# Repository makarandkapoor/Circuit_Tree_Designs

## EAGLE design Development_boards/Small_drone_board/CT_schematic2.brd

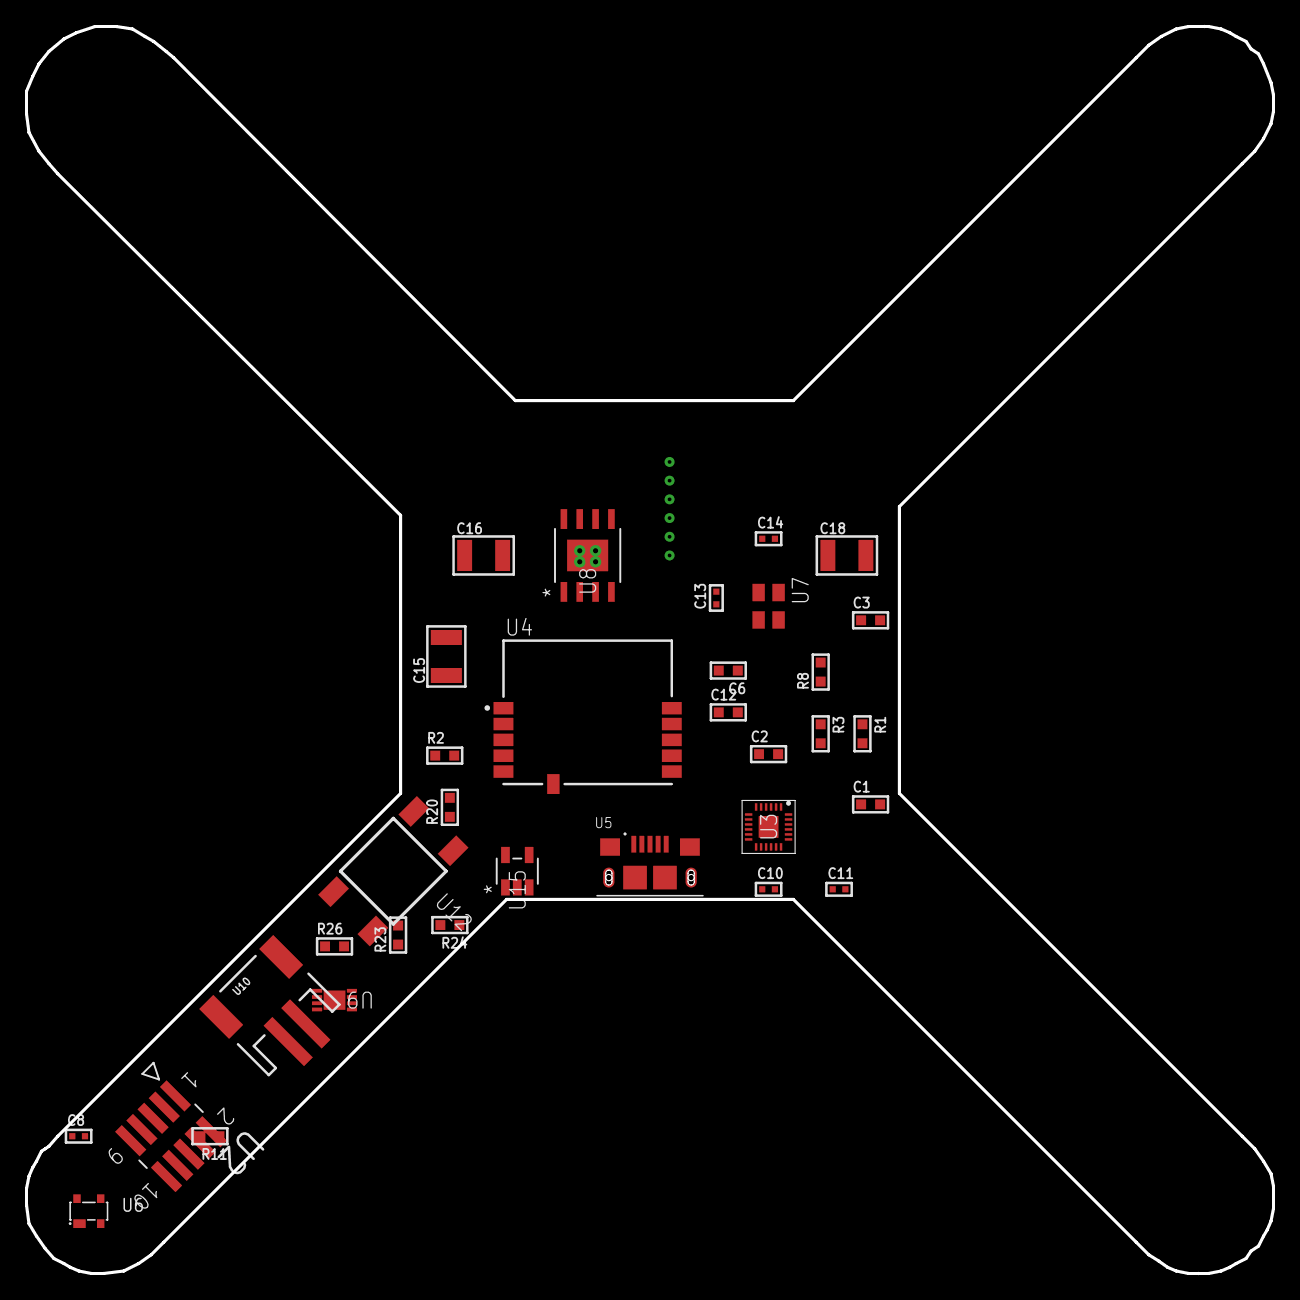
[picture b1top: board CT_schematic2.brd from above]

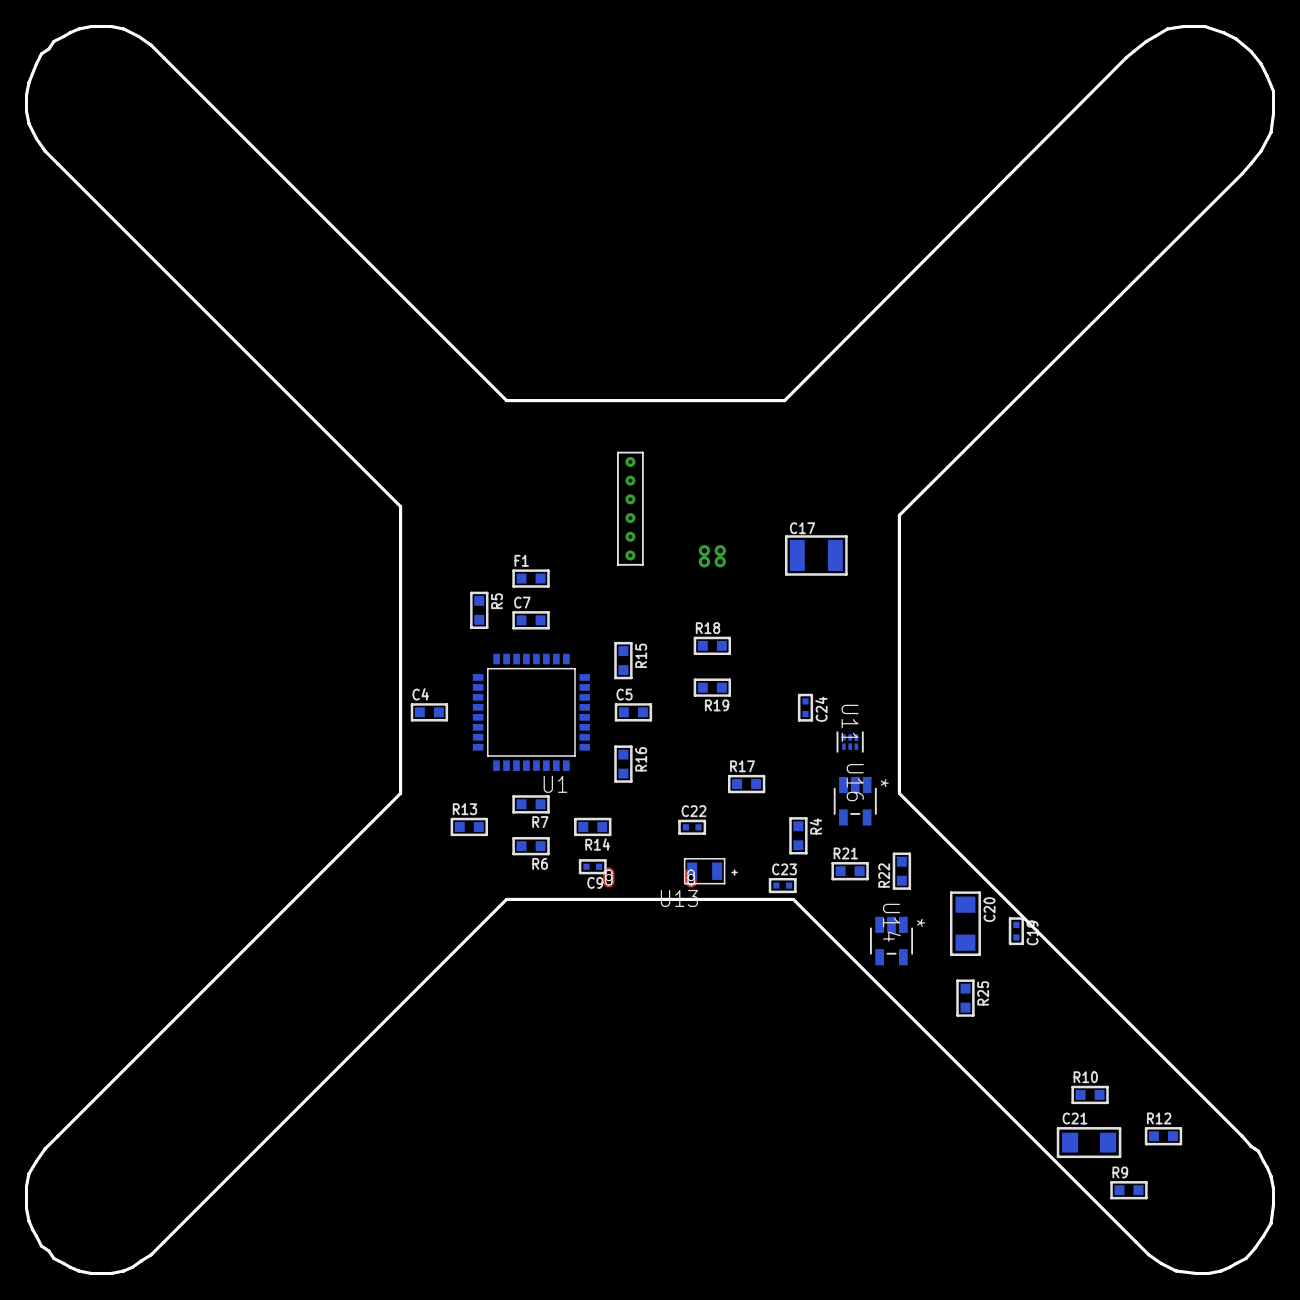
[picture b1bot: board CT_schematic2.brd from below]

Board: 2 copper layers, 100.0 x 100.0 mm, 68 parts (35 on the bottom side), 40 nets, no tracks yet.

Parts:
C1: c1; C0603
C2: c2; C0603
C3: c3; C0603
C4: c4; C0603
C5: c5; C0603
C6: c6; C0603
C7: c7; C0603
C8: c8; C0402
C9: c9; C0402
C10: c10; C0402
C11: c11; C0402
C12: c12; C0603
C13: c13; C0402
C14: c14; C0402
C15: c15; C1210
C16: c16; C1210
C17: c17; C1210
C18: c18; C1210
C19: c19; C0402
C20: c20; C1206
C21: c21; C1206
C22: c22; C0402
C23: c23; C0402
C24: c24; C0402
F1: f1; L0603
R1: r1; R0603
R2: r2; R0603
R3: r3; R0603
R4: r4; R0603
R5: r5; R0603
R6: r6; R0603
R7: r7; R0603
R8: r8; R0603
R9: r9; R0603
R10: r10; R0603
R11: r11; R0603
R12: r12; R0603
R13: r13; R0603
R14: r14; R0603
R15: r15; R0603
R16: r16; R0603
R17: r17; R0603
R18: r18; R0603
R19: r19; R0603
R20: r20; R0603
R21: r21; R0603
R22: r22; R0603
R23: r23; R0603
R24: r24; R0603
R25: r25; R0603
R26: r26; R0603
U1: u1; LQFP32
U2: u2; SAMTEC_FTSH-105-01-L-DV-K
U3: u3; QFN24_2
U4: u4; XCVR_SPBTLE-RF
U5: u5; FCI_10118193-0001LF
U6: u6; SOT143B
U7: u7; ASEK
U8: u8; SOIC-8_EP
U9: u9; DFN8_2X3MC
U10: u10; JST-2-SMD
U11: u11; SON-6
U12: u12; SW_4-1437565-2
U13: u13; LGM67K-G1J2-24-Z
U14: u14; NC7SZ125M5X
U15: u15; NC7SZ125M5X
U16: u16; NC7SZ125M5X
U17: u17; DUMMY_PACKAGE_150

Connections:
CLK_U1_2: U1.2, U7.3
GND: C1.2, C2.2, C3.2, C4.2, C5.2, C6.2, C7.2, C8.2, C9.2, C10.2, C11.2, C12.2, C13.2, C14.2, C15.2, C16.2, C17.2, C18.2, C19.2, C20.2, C21.2, C22.2, C23.2, C24.2, R2.2, R8.2, R12.2, R16.2, R17.2, R19.2, R22.2, R24.2, R25.2, U1.16, U1.32, U2.3, U2.5, U3.18, U3.20, U3.25, U4.6, U5.5, U5.6, U5.7, U5.8, U5.9, U6.1, U7.2, U8.7, U8.EPAD, U9.6, U9.9, U10.2, U11.2, U13.C, U14.2, U14.3, U15.1, U15.3, U16.1, U16.3, U17.1
INPUT_USBPOWER_5V: C20.1, R26.2, U5.1, U6.4, U9.1, U9.2
NET_U1_4: R5.1, U1.4, U16.4
NET_U1_5: C6.1, C7.1, F1.1, U1.5
NET_U1_27: R3.1, U1.27, U13.A
NET_U1_28: R1.1, U1.28, U12.3, U12.4
NET_U1_29: R6.1, U1.29, U3.23
NET_U1_30: R7.1, U1.30, U3.24
NET_U1_31: R8.1, U1.31
NET_U2_9: R12.1, U2.9
NET_U3_9: R14.1, U3.9
NET_U3_10: C9.1, U3.10
NET_U3_22: R13.1, U3.22
NET_U4_11: R4.1, U4.11, U15.4
NET_U8_4: R18.2, R19.1, U8.4
NET_U9_5: R26.1, U9.5
NET_U9_8: R25.1, U9.8
NET_U11_1: R21.1, R22.1, U11.1
NET_U11_3: R23.2, R24.1, U11.3
NET_U11_4: R20.1, U11.4, U14.4, U15.2, U16.2
NET_U12_1: R2.1, U12.1, U12.2
PROC_GPIO_TO_U3_FSYNC: U1.6, U3.11
PROC_GPIO_TO_U3_INT_B: U1.3, U3.12
PROC_GPIO_TO_U4_SPI_IRQ: R17.1, U1.7, U4.4
PROC_PA2: U1.8, U17.2
PROC_PA3: U1.9, U17.3
PROC_PB0: U1.14, U17.4
PROC_PB1: U1.15, U17.5
PROC_SPI1_MISO: U1.12, U4.8
PROC_SPI1_MOSI: U1.13, U4.9
PROC_SPI1_NSS: R15.1, U1.10, U4.10
PROC_SPI1_SCK: R16.1, U1.11, U4.7
PROC_SYS_SWCLK: R10.1, U1.24, U2.4
PROC_SYS_SWDIO: R11.1, U1.23, U2.2
PROC_USB_DM: U1.21, U5.2, U6.3
PROC_USB_DP: U1.22, U5.3, U6.2
RST_OUT_U2_JTAG_RST_B: R9.1, U2.10, U14.1
VCC_S1_3V7: C15.1, C16.1, C21.1, U8.5, U8.8, U9.3, U9.4, U10.1
VCC_TIER1_3V3: C1.1, C2.1, C3.1, C4.1, C5.1, C8.1, C10.1, C11.1, C12.1, C13.1, C14.1, C17.1, C18.1, C19.1, C22.1, C23.1, C24.1, F1.2, R1.2, R3.2, R4.2, R5.2, R6.2, R7.2, R9.2, R10.2, R11.2, R13.2, R14.2, R15.2, R18.1, R20.2, R21.2, R23.1, U1.1, U1.17, U2.1, U3.1, U3.8, U3.13, U4.5, U7.4, U8.1, U11.6, U14.5, U15.5, U16.5

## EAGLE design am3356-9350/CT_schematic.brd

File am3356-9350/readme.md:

## Introduction
This design is a demo design example auto generated through scripts at circuit-tree.com server. 
Circuit Tree designs are dynamic which means designs, symbols and placement is generated dynamically
The scripts randonly selects parts, peripheral interfaces, type and value of power input to the board to be created.

## Folder contents
In this folder eagle, altium and orcad schematic files , bill of material, board component placement file 
pictures from various dxf file which are auto generated through circuit tree server are present.

## Additional references
Generate embedded hardware designs through [Circuit Tree](http://circuit-tree.com/) schematics and board placement file instantly. 
Use autorouter to complete your the final board file.

## Circuit Description
Circuit Description: Design uses a controller from Texas Instruments with part number AM3356BZCZA80 and following parts in the 
design:
- 10100565 from Amphenol
- FTSH-105-01-L-DV-K from Samtec
- LAN8710AI-EZK from Microchip
- 7498011122R from WURTH ELEKTRONIK
- AT24C02D-SSHM-T from Atmel
- S29VS256RABBHW000 from Spansion
- ABS07-32.768KHZ-7-T from ABRACON
- ABLS-25.000MHZ-B2F-T from ABRACON
- ASDMB-24.000MHZ-EC-T from abracon
- LP2954AIMX/NOPB from TI
- LP3878SDX-ADJ/NOPB  from TI
- LP2951ACSDX/NOPB from TI
- LP3878SDX-ADJ/NOPB  from TI
- LTC3601EUD#PBF from Linear Tech
- LTC3601EUD#PBF from Linear Tech
- LTC3601EUD#PBF from Linear Tech
- LTC2928CUHF#PBF from Linear Tech
- IRF8306MTRPbF from Infineon
- IRF8306MTRPbF from Infineon
- IRF8306MTRPbF from Infineon
- IRF8306MTRPbF from Infineon
- PJ-037B from CUI Inc.
- 4-1437565-2 from TE connectivity
- Q65110A2395 from osram
- nc7sz125m5x from On Semi
- nc7sz125m5x from On Semi
- nc7sz125m5x from On Semi
- nc7sz125m5x from On Semi

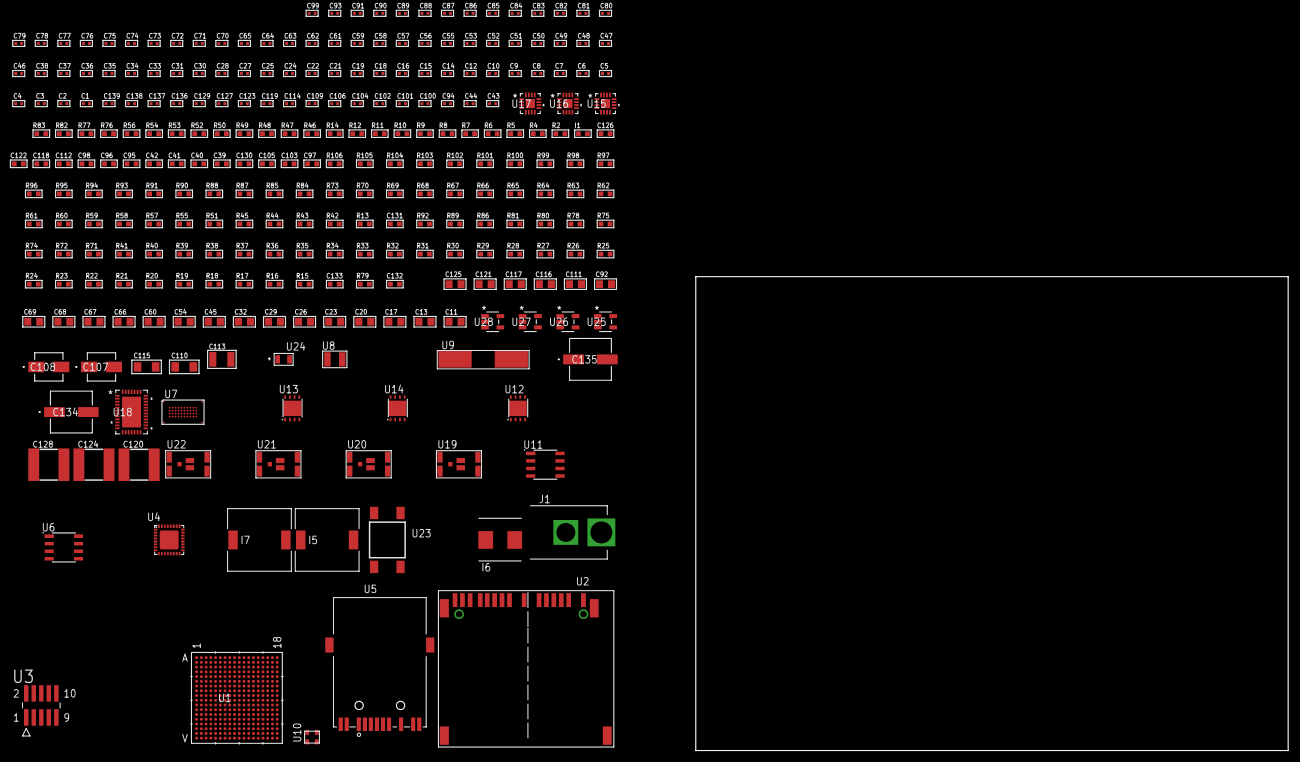
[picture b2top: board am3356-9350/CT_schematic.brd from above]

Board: 2 copper layers, 100.0 x 80.0 mm, 276 parts (0 on the bottom side), 180 nets, no tracks yet.

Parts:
C1, C6, C7, C65, C70, C71, C72, C73, C74, C75, C76, C77, C78, C79, C80, C81, C82, C83, C84, C85, C86, C87, C88, C89, C90, C91, C93, C102, C104, C119, C123, C127, C129: 1e-07; C0402
C2, C3, C4, C5, C8, C9, C10, C12, C14, C15, C16, C18, C19, C21, C22, C24, C25, C27, C28, C30, C31, C33, C34, C35, C36, C37, C38, C46, C47, C48, C49, C50, C51, C52, C53, C55, C56, C57, C58, C59, C61, C62, C63, C64, C101, C106, C109, C114, C136, C137, C138, C139: 1e-08; C0402
C11, C13, C17, C20, C23, C26, C29, C32, C45, C54, C60, C66, C67, C68, C69, C92, C111, C116, C117, C121, C125: 1e-05; C0805
C39, C40, C41, C42, C95, C96, C98, C112, C118, C122, C126: 1e-06; C0603
C43, C44: 1.2e-11; C0402
C94: 2.2e-08; C0402
C97: 4.7e-10; C0603
C99, C100: 1e-11; C0402
C103, C105, C130: 2.2e-06; C0603
C107: 1e-06; EXV-9B
C108: 2.2e-06; EXV-9B
C110, C115: 1e-05; C1206
C113: 1e-05; C1210
C120, C124, C128: 6.8e-05; 2220
C131: 2.45e-08; R0603
C132: 2.8258362168397e-09; R0603
C133: 7.105e-09; R0603
C134, C135: 0.0001; EXV-9H
I1: 97.0; R0603
I5: 2.5e-06; DR1040
I6: 3.3e-06; WE-HCI_7030/7040/7050
I7: 3.8e-06; DR1040
J1: PJ-037B; PJ-037B_PACKAGE
R2, R77, R83: 1000.0; R0603
R4, R5, R6, R7: 4700.0; R0603
R8, R9, R10, R11: 2200.0; R0603
R12: 22.0; R0603
R13, R42, R43, R44, R45, R55, R57, R58, R59, R60, R61, R62, R63, R64, R65, R66, R67, R68, R69, R70, R93, R95, R96, R101, R102, R103, R104, R105: 10000.0; R0603
R14, R52, R53, R54, R56: 49.9; R0603
R15, R16, R17, R18, R19, R20, R21, R22, R23, R24, R25, R26, R27, R28, R29, R30, R31, R32, R33, R34, R35, R36, R37, R38, R39, R40, R41, R71, R72, R74, R75, R78, R80, R81: 100000.0; R0603
R46: 5.0; R0603
R47, R48: 0.1; R0603
R49, R50: 200.0; R0603
R51: 12100.0; R0603
R73: 47000.0; R0603
R76: 360.0; R0603
R79: 153694.38; R0603
R82: 100.0; R0603
R84, R87, R90: 20000.0; R0603
R85: 22600.0; R0603
R86, R89, R92: 300000.0; R0603
R88: 39000.0; R0603
R91: 91000.0; R0603
R94, R106: 75000.0; R0603
R97, R98, R99, R100: 95300.0; R0603
U1: AM3356BZCZA80; LFBGA324
U2: 10100565
U3: FTSH-105-01-L-DV-K; SAMTEC_FTSH-105-01-L-DV-K
U4: LAN8710AI-EZK; QFN-32
U5: 7498011122R
U6: AT24C02D-SSHM-T; AT24C02D
U7: S29VS256RABBHW000
U8: ABS07-32.768KHZ-7-T
U9: ABLS-25.000MHZ-B2F-T
U10: ASDMB-24.000MHZ-EC-T; ASDMB-XX.XXXXMHZ-XX-XX-XXX
U11: LP2954AIMX/NOPB; LP2954
U12, U14: LP3878SDX-ADJ/NOPB; WSON-8
U13: LP2951ACSDX/NOPB; WSON-8
U15, U16, U17: LTC3601EUD#PBF; QFN-16_EP
U18: LTC2928CUHF#PBF; QFN-38_UHF
U19, U20, U21, U22: IRF8306MTRPbF; IRF8306MTRPBF
U23: 4-1437565-2; SW_4-1437565-2
U24: Q65110A2395; LGM67K-G1J2-24-Z
U25, U26, U27, U28: nc7sz125m5x; NC7SZ125M5X

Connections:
CLK_CRYSTAL_U1_A4: C44.1, U1.A4, U8.2
CLK_CRYSTAL_U1_A6: C43.1, U1.A6, U8.1
CLK_CRYSTAL_U4_4: C100.1, U4.4, U9.2
CLK_CRYSTAL_U4_5: C99.1, U4.5, U9.1
CLK_U1_V10: U1.V10, U10.3
GND: C1.2, C2.2, C3.2, C4.2, C5.2, C6.2, C7.2, C8.2, C9.2, C10.2, C11.2, C12.2, C13.2, C14.2, C15.2, C16.2, C17.2, C18.2, C19.2, C20.2, C21.2, C22.2, C23.2, C24.2, C25.2, C26.2, C27.2, C28.2, C29.2, C30.2, C31.2, C32.2, C33.2, C34.2, C35.2, C36.2, C37.2, C38.2, C39.2, C40.2, C41.2, C42.2, C43.2, C44.2, C45.2, C46.2, C47.2, C48.2, C49.2, C50.2, C51.2, C52.2, C53.2, C54.2, C55.2, C56.2, C57.2, C58.2, C59.2, C60.2, C61.2, C62.2, C63.2, C64.2, C65.2, C66.2, C67.2, C68.2, C69.2, C70.2, C71.2, C72.2, C73.2, C74.2, C75.2, C76.2, C77.2, C78.2, C79.2, C80.2, C81.2, C82.2, C83.2, C84.2, C85.2, C86.2, C87.2, C88.2, C89.2, C90.2, C91.2, C92.2, C93.2, C94.2, C95.2, C96.2, C97.2, C98.2, C99.2, C100.2, C101.2, C102.2, C103.2, C104.2, C105.2, C106.2, C107.2, C108.2, C109.2, C110.2, C111.2, C112.2, C113.2, C114.2, C115.2, C116.2, C117.2, C118.2, C120.1, C120.2, C121.2, C122.2, C124.1, C124.2, C125.2, C126.2, C128.1, C128.2, C129.2, C130.2, C131.2, C132.2, C133.2, C134.2, C135.2, C136.2, C137.2, C138.2, C139.2, J1.2, R2.2, R13.2, R14.2, R21.2, R22.2, R24.2, R25.2, R26.2, R27.2, R28.2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
NET_U1_A10: R6.1, U1.A10, U28.4
NET_U1_B4: R13.1, U1.B4
NET_U1_C10: C42.1, U1.C10
NET_U1_C16: R8.1, U1.C16, U6.6
NET_U1_C17: R9.1, U1.C17, U6.5
NET_U1_D6: C40.1, U1.D6
NET_U1_D9: C39.1, U1.D9
NET_U1_D11: C41.1, U1.D11
NET_U1_F15: U23.3, U23.4
NET_U1_J3: R14.1, U1.J3
NET_U1_J4: C1.1, C6.1, C7.1, U1.J4
NET_U1_M17: R11.1, U1.M17, U4.16
NET_U1_M18: R10.1, U1.M18, U4.17
NET_U1_R1: R15.1, U1.R1
NET_U1_R2: R16.1, U1.R2
NET_U1_R3: R17.1, U1.R3
NET_U1_R4: R18.1, U1.R4
NET_U1_R15: C5.1, U1.R15
NET_U1_R16: C4.1, U1.R16
NET_U1_T1: R19.1, U1.T1
NET_U1_T2: R20.1, U1.T2
NET_U1_T3: R21.1, U1.T3
NET_U1_T4: R22.1, U1.T4
NET_U1_U1: R23.1, U1.U1
NET_U1_U2: R24.1, U1.U2
NET_U1_U3: R25.1, U1.U3
NET_U1_U4: R26.1, U1.U4
NET_U1_V2: R27.1, U1.V2
NET_U2_18: U2.18, U2.19
NET_U3_9: R46.1, U3.9
NET_U4_1: C95.1, I1.1, R52.2, R53.2, R54.2, R56.2, U4.1, U4.27
NET_U4_6: C96.1, C97.1, U4.6
NET_U4_18: R55.1, U4.18
NET_U4_19: R4.1, U4.19, U26.4
NET_U4_32: R51.1, U4.32
NET_U5_1: R52.1, U4.29, U5.1
NET_U5_3: R50.2, R53.1, U4.28, U5.3
NET_U5_4: R54.1, U4.31, U5.4
NET_U5_5: C94.1, U5.2, U5.5
NET_U5_6: R56.1, U4.30, U5.6
NET_U5_8: R48.1, U5.8
NET_U5_9: R50.1, U5.9
NET_U5_11: U4.2, U5.11
NET_U5_12: R49.1, U5.12
NET_U5_13: R47.1, U5.13, U5.14
NET_U6_1: R64.1, U6.1
NET_U6_2: R65.1, U6.2
NET_U6_3: R66.1, U6.3
NET_U6_7: R63.1, U6.7
NET_U7_D8: R5.1, U7.D8, U27.4
NET_U11_3: R72.1, U11.3
NET_U11_5: R71.1, U11.5
NET_U11_7: R73.2, R74.1, U11.7
NET_U12_1: C109.1, U12.1
NET_U12_6: R76.2, R77.1, U12.6
NET_U12_8: R75.1, U12.8
NET_U13_5: R78.1, U13.5
NET_U13_7: R79.2, R80.1, U13.7
NET_U14_1: C114.1, U14.1
NET_U14_6: R82.2, R83.1, U14.6
NET_U14_8: R81.1, U14.8
NET_U15_3: C119.2, I5.1, U15.3, U15.4
NET_U15_6: C119.1, U15.6
NET_U15_7: C118.1, U15.7, U15.12
NET_U15_10: R86.1, U15.10
NET_U15_11: R84.1, R85.1, U15.11
NET_U15_ATNET_3: I5.2, R85.2
NET_U16_3: C123.2, I6.1, U16.3, U16.4
NET_U16_6: C123.1, U16.6
NET_U16_7: C122.1, U16.7, U16.12
NET_U16_10: R89.1, U16.10
NET_U16_11: R87.1, R88.1, U16.11
NET_U16_ATNET_3: I6.2, R88.2
NET_U17_3: C127.2, I7.1, U17.3, U17.4
NET_U17_6: C127.1, U17.6
NET_U17_7: C126.1, U17.7, U17.12
NET_U17_10: R92.1, U17.10
NET_U17_11: R90.1, R91.1, U17.11
NET_U17_ATNET_3: I7.2, R91.2
NET_U18_3: R102.1, U18.3
NET_U18_6: R97.1, U18.6
NET_U18_7: R98.1, U18.7
NET_U18_8: R99.1, U18.8
NET_U18_9: R100.1, U18.9
NET_U18_16: R101.1, R106.1, U18.16
NET_U18_18: R96.1, U18.18
NET_U18_19: R95.1, U18.19, U18.20
NET_U18_21: R93.1, R94.1, U18.21, U25.4, U26.2, U27.2, U28.2
NET_U18_22: C129.1, R93.2, R95.2, R96.2, U18.11, U18.22
NET_U18_26: C132.1, U18.26
NET_U18_27: C131.1, U18.27
NET_U18_28: C133.1, U18.28
NET_U18_30: R105.1, U18.30
NET_U18_32: R104.1, U18.32
NET_U18_38: R103.1, U18.38
NET_U19_3: U18.2, U19.3
NET_U20_3: U18.37, U20.3
NET_U21_3: U18.31, U21.3
NET_U22_3: U18.29, U22.3
NET_U23_1: R2.1, U23.1, U23.2
PROC_GPMC_A17: R28.1, U1.V3, U7.D4
PROC_GPMC_A18: R29.1, U1.V4, U7.C11
PROC_GPMC_A19: R30.1, U1.T5, U7.D10
PROC_GPMC_A20: U1.R14, U7.C10
PROC_GPMC_A21: U1.V15, U7.D5
PROC_GPMC_A22: U1.G15, U7.C4
PROC_GPMC_A23: U1.G16, U7.C12
PROC_GPMC_A24: U1.G17, U7.D7
PROC_GPMC_AD0: U1.U7, U7.F3
PROC_GPMC_AD1: U1.V7, U7.F4
PROC_GPMC_AD2: U1.R8, U7.E6
PROC_GPMC_AD3: U1.T8, U7.E7
PROC_GPMC_AD4: U1.U8, U7.F8
PROC_GPMC_AD5: U1.V8, U7.F9
PROC_GPMC_AD6: U1.R9, U7.E10
PROC_GPMC_AD7: U1.T9, U7.E11
PROC_GPMC_AD8: U1.U10, U7.E4
PROC_GPMC_AD9: U1.T10, U7.E5
PROC_GPMC_AD10: U1.T11, U7.F6
PROC_GPMC_AD11: U1.U12, U7.F7
PROC_GPMC_AD12: U1.T12, U7.E8
PROC_GPMC_AD13: U1.R12, U7.E9
PROC_GPMC_AD14: U1.V13, U7.F11
PROC_GPMC_AD15: U1.U13, U7.F12
PROC_GPMC_ADVN_ALE: U1.R7, U7.D6
PROC_GPMC_CLK: U1.U9, U7.C6
PROC_GPMC_CSN0: R68.1, U1.V6, U7.D11
PROC_GPMC_OEN_REN: R70.1, U1.T7, U7.E12
PROC_GPMC_WAIT0: R67.1, U1.T17, U7.C3
PROC_GPMC_WEN: R69.1, U1.U6, U7.C8
PROC_MII1_COL: R59.1, U1.H16, U4.15
PROC_MII1_CRS: U1.H17, U4.14
PROC_MII1_RXD0: R57.1, U1.M16, U4.11
PROC_MII1_RXD1: R58.1, U1.L15, U4.10
PROC_MII1_RXD2: U1.L16, U4.9
PROC_MII1_RXD3: R62.1, U1.L17, U4.8
PROC_MII1_RX_CLK: R61.1, U1.L18, U4.7
PROC_MII1_RX_DV: U1.J17, U4.26
PROC_MII1_RX_ER: R60.1, U1.J15, U4.13
PROC_MII1_TXD0: U1.K17, U4.22
PROC_MII1_TXD1: U1.K16, U4.23
PROC_MII1_TXD2: U1.K15, U4.24
PROC_MII1_TXD3: U1.J18, U4.25
PROC_MII1_TX_CLK: U1.K18, U4.20
PROC_MII1_TX_EN: U1.J16, U4.21
PROC_MMC2_CLK: R12.2, R31.1, U1.V12, U2.8
PROC_MMC2_CLK_R: R12.1, U1.V12
PROC_MMC2_DAT0: R34.1, U1.V14, U2.4
PROC_MMC2_DAT1: R35.1, U1.U14, U2.3
PROC_MMC2_DAT2: R36.1, U1.T14, U2.15
PROC_MMC2_DAT3: R37.1, U1.U18, U2.14
PROC_MMC2_DAT4: R38.1, U1.U15, U2.13
PROC_MMC2_DAT5: R39.1, U1.T15, U2.11
PROC_MMC2_DAT6: R40.1, U1.V16, U2.7
PROC_MMC2_DAT7: R41.1, U1.U16, U2.5
PROC_MMC2_SDCD: R32.1, U1.U17, U2.2
PROC_MMC2_SDWP: R33.1, U1.A16, U2.1
PROC_TCK: R45.1, U1.A12, U3.4
PROC_TDI: R43.1, U1.B11, U3.8
PROC_TDO: U1.A11, U3.6
PROC_TMS: R44.1, U1.C11, U3.2
RST_OUT_U3_JTAG_RST_B: R42.1, U3.10, U25.1
VCC_9V3: C130.1, C134.1, C135.1, J1.1, R106.2, U18.23, U19.1, U19.2, U19.6, U19.7, U20.1, U20.2, U20.6, U20.7, U21.1, U21.2, U21.6, U21.7, U22.1, U22.2, U22.6, U22.7
VCC_S1_9V3: C107.1, R72.2, U11.8, U19.4, U19.5
VCC_S2_9V3: C110.1, R75.2, U12.4, U20.4, U20.5
VCC_S3_9V3: C112.1, U13.8, U21.4, U21.5
VCC_S4_9V3: C115.1, C117.1, C121.1, C125.1, R81.2, U14.4, U15.15, U15.16, U16.15, U16.16, U17.15, U17.16, U22.4, U22.5
VCC_TIER1_1V8: C2.1, C8.1, C9.1, C10.1, C11.1, C12.1, C13.1, C14.1, C15.1, C16.1, C60.1, C61.1, C62.1, C63.1, C64.1, C91.1, C92.1, C106.1, C108.1, C136.1, C137.1, C138.1, C139.1, R31.2, R32.2, R33.2, R34.2, R35.2, R36.2, R37.2, R38.2, R39.2, R40.2, R41.2, R71.2, R73.1, U1.D7, U1.D10, U1.E6, U1.E7, U1.E9, U1.E14, U1.F9, U1.H15, U1.K13, U1.N6, U1.N16, U1.P9, U1.P14, U1.R10, U1.R11, U2.9, U10.4, U11.1, U25.5, U26.5, U27.5, U28.5
VCC_TIER2_1V35: C65.1, C66.1, C67.1, C68.1, C69.1, C70.1, C71.1, C72.1, C73.1, C74.1, C75.1, C76.1, C77.1, C78.1, C79.1, C80.1, C81.1, C82.1, C83.1, C84.1, C85.1, C86.1, C87.1, C88.1, C89.1, C90.1, C111.1, R76.1, U1.E5, U1.F5, U1.G5, U1.H5, U1.J5, U1.K5, U1.L5, U12.5
VCC_TIER3_3V3: C3.1, C113.1, R78.2, R79.1, U1.N15, U13.1
VCC_TIER4_1V1: C45.1, C46.1, C47.1, C48.1, C49.1, C50.1, C51.1, C52.1, C53.1, C116.1, R82.1, U1.F6, U1.F7, U1.G6, U1.G7, U1.G10, U1.H11, U1.J12, U1.K6, U1.K8, U1.K12, U1.L6, U1.L7, U1.L8, U1.L9, U1.M11, U1.M13, U1.N8, U1.N9, U1.N12, U1.N13, U14.5
VCC_TIER4_1V8: C17.1, C18.1, C19.1, C20.1, C21.1, C22.1, C23.1, C24.1, C25.1, C26.1, C27.1, C28.1, C29.1, C30.1, C31.1, C32.1, C33.1, C34.1, C35.1, C36.1, C37.1, C38.1, C93.1, C98.1, C101.1, C102.1, C103.1, C104.1, C105.1, C124.2, I6.2, R4.2, R5.2, R6.2, R7.2, R8.2, R9.2, R10.2, R11.2, R15.2, R16.2, R17.2, R18.2, R19.2, R20.2, R23.2, R42.2, R43.2, R44.2, R55.2, R57.2, R58.2, R59.2, R60.2, R61.2, R64.2, R67.2, R68.2, R69.2, R70.2, R88.2, U1.E10, U1.E11, U1.E12, U1.E13, U1.F14, U1.G14, U1.H14, U1.J14, U1.K14, U1.L14, U1.N5, U1.P5, U1.P6, U1.P7, U1.P8, U1.P10, U1.P11, U1.P12, U1.P13, U3.1, U4.12, U6.8, U7.C7, U7.D3, U7.F10, U16.8
VCC_TIER4_1V26: C54.1, C55.1, C56.1, C57.1, C58.1, C59.1, C120.2, I5.2, R85.2, U1.A2, U1.F10, U1.F11, U1.F12, U1.F13, U1.G13, U1.H13, U1.J13, U15.8
VCC_TIER4_3V3: C128.2, I1.2, I7.2, R91.2, U17.8

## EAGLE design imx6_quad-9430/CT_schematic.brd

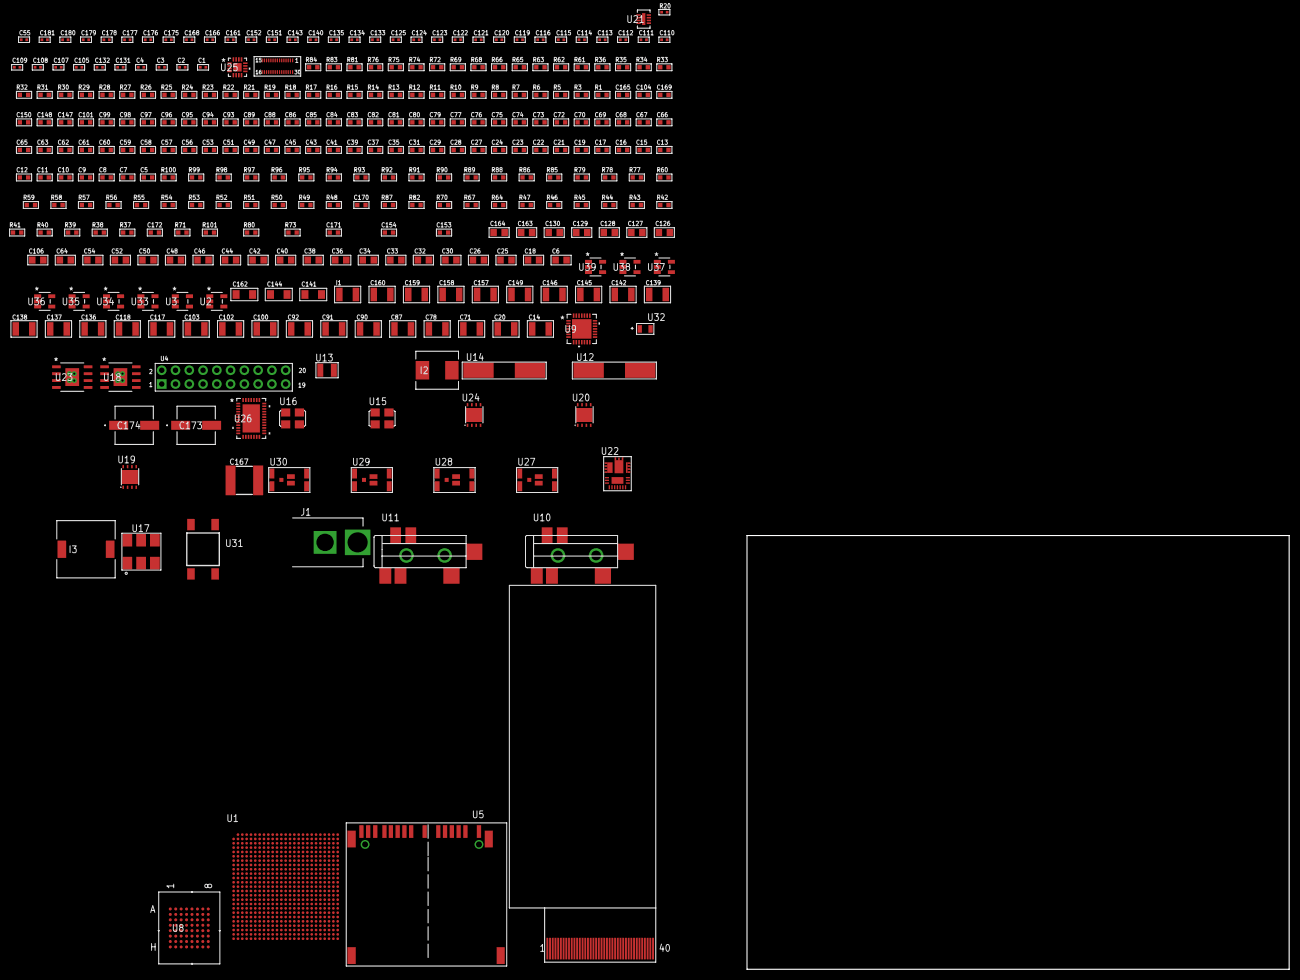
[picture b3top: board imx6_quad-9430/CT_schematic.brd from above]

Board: 2 copper layers, 100.0 x 80.0 mm, 321 parts (0 on the bottom side), 229 nets, no tracks yet.

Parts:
C1, C2, C3, C4: 1.2e-11; C0402
C5, C7, C8, C9, C10, C11, C12, C13, C15, C16, C17, C19, C21, C22, C23, C24, C27, C28, C29, C31, C35, C37, C39, C41, C43, C45, C47, C49, C51, C53, C56, C57, C58, C59, C60, C61, C62, C63, C65, C66, C67, C68, C69, C70, C72, C73, C74, C75, C76, C77, C79, C80, C81, C82, C83, C84, C85, C86, C88, C89, C93, C94, C95, C96, C97, C98, C99, C101, C148: 2.2e-07; C0603
C6, C18, C25, C26, C30, C32, C33, C34, C36, C54, C64, C106, C126, C127, C128, C129, C130, C163, C164: 1e-05; C0805
C14, C20, C71, C78, C87, C90, C91, C92, C100, C102, C103, C117, C118: 2.2e-05; C1210
C38, C40, C42, C44, C46, C48, C50, C52: 4.7e-06; C0805
C55, C105, C107, C108, C109, C110, C111, C112, C113, C114, C121, C122, C123, C124, C125, C151, C152, C166, C168: 1e-07; C0402
C104, C165: 1e-06; C0603
C115, C116, C133, C134, C135, C140, C143, C161, C175, C176, C177, C178, C179, C180, C181: 1e-08; C0402
C119, C120: 1e-09; C0402
C131, C132: 2.2e-11; C0402
C136, C137, C138, C139, C142, C145, C146, C157, C158, C159, C160: 1e-05; C1210
C141, C144, C162: 1e-05; C1206
C147, C150, C169: 2.2e-06; C0603
C149: 0.0001; C1210
C153: 1.0231891044381e-09; R0603
C154: 3.4881446742207e-08; R0603
C167: 6.8e-05; 2220
C170: 2.45e-08; R0603
C171: 2.8258362168397e-09; R0603
C172: 7.105e-09; R0603
C173, C174: 0.0001; EXV-9H
I1: 1e-05; L1210
I2: 6.8e-07; IND25X25CZ
I3: 2.5e-06; DR1040
J1: PJ-037B; PJ-037B_PACKAGE
R1, R5, R6, R7, R8, R9, R10, R11, R12, R14, R15, R26, R27: 4700.0; R0603
R3, R25, R66, R69, R84: 1000.0; R0603
R13, R63, R81: 2200.0; R0603
R16, R17: 6040.0; R0603
R18: 1600.0; R0603
R19: 200.0; R0603
R20: 191.0; R0402
R21, R22, R23, R28, R29, R30, R31, R32, R33, R34, R35, R36, R72: 0.1; R0603
R24: 240.0; R0603
R37, R38, R39, R40, R41, R42, R43, R44, R45, R46, R47, R64, R67, R70, R82: 100000.0; R0603
R48, R49, R50, R51, R52, R53, R54, R55, R56, R57, R88, R90, R91, R96, R97, R98, R99, R100: 10000.0; R0603
R58, R59, R60: 47000.0; R0603
R61: 680.0; R0603
R62: 910.0; R0603
R65: 1800.0; R0603
R68: 2231.0; R0603
R71: 1600000.0; R0603
R73: 4030.2416170974; R0603
R74: 2700.0; R0603
R75, R83: 510.0; R0603
R76: 130.0; R0603
R77: 39000.0; R0603
R78: 49900.0; R0603
R79, R85: 20000.0; R0603
R80: 3155.1219512195; R0603
R86: 91000.0; R0603
R87: 300000.0; R0603
R89: 75000.0; R0603
R92, R93, R94, R95: 95300.0; R0603
R101: 40090.909090909; R0603
U1: MCIMX6Q7CVT08AD; BGA624N80P25X25_210X210X20
U2, U3, U33, U34, U35, U36, U37, U38, U39: nc7sz125m5x; NC7SZ125M5X
U4: arducam_ov2640; ARDUCAM
U5: 10100565
U6: ER-TFT018-2
U7: LH430WV2-SD01
U8: mt28ew512aba1HPC-0AAT; LBGA-64
U9: WM8731CLSEFL; QFN-28
U10, U11: SJ-43515TS-SMT-TR
U12: ABLS-24.000MHZ-B4-T
U13: ABS07-32.768KHZ-7-T
U14: ABLS-12.288MHZ-B4-T
U15: ASFL1-25MHZ-NCS; ASFL1
U16: ASFL1-50MHZ-NCS; ASFL1
U17: shpcie100; SHPCIE100
U18, U23: MIC5234YME; SOIC-8_EP
U19, U20, U24: LP3878SDX-ADJ/NOPB; WSON-8
U21: LT3494AEDDB#TRMPBF; DFN-8_DDB
U22: IR3899MTR1PBF
U25: LTC3601EUD#PBF; QFN-16_EP
U26: LTC2928CUHF#PBF; QFN-38_UHF
U27, U28, U29, U30: IRF8306MTRPbF; IRF8306MTRPBF
U31: 4-1437565-2; SW_4-1437565-2
U32: Q65110A2395; LGM67K-G1J2-24-Z

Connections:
CLK_CRYSTAL_U1_A7: C2.1, U1.A7, U12.1
CLK_CRYSTAL_U1_B7: C1.1, U1.B7, U12.2
CLK_CRYSTAL_U1_C9: C3.1, U1.C9, U13.2
CLK_CRYSTAL_U1_D9: C4.1, U1.D9, U13.1
CLK_CRYSTAL_U9_1: C131.1, U9.1, U14.1
CLK_CRYSTAL_U9_2: C132.1, U9.2, U14.2
CLK_U1_C7: U1.C7, U17.4
CLK_U1_D7: U1.D7, U17.5
CLK_U1_V22: U1.V22, U16.3
CLK_U4_8: U4.8, U15.3
GND: C1.2, C2.2, C3.2, C4.2, C5.2, C6.2, C7.2, C8.2, C9.2, C10.2, C11.2, C12.2, C13.2, C14.2, C15.2, C16.2, C17.2, C18.2, C19.2, C20.2, C21.2, C22.2, C23.2, C24.2, C25.2, C26.2, C27.2, C28.2, C29.2, C30.2, C31.2, C32.2, C33.2, C34.2, C35.2, C36.2, C37.2, C38.2, C39.2, C40.2, C41.2, C42.2, C43.2, C44.2, C45.2, C46.2, C47.2, C48.2, C49.2, C50.2, C51.2, C52.2, C53.2, C54.2, C55.2, C56.2, C57.2, C58.2, C59.2, C60.2, C61.2, C62.2, C63.2, C64.2, C65.2, C66.2, C67.2, C68.2, C69.2, C70.2, C71.2, C72.2, C73.2, C74.2, C75.2, C76.2, C77.2, C78.2, C79.2, C80.2, C81.2, C82.2, C83.2, C84.2, C85.2, C86.2, C87.2, C88.2, C89.2, C90.2, C91.2, C92.2, C93.2, C94.2, C95.2, C96.2, C97.2, C98.2, C99.2, C100.2, C101.2, C102.2, C103.2, C104.2, C105.2, C106.2, C107.2, C108.2, C109.2, C110.2, C111.2, C112.2, C113.2, C114.2, C115.2, C116.2, C120.2, C121.2, C122.2, C123.2, C124.2, C125.2, C126.2, C127.2, C128.2, C129.2, C130.2, C131.2, C132.2, C133.2, C134.2, C135.2, C136.2, C137.2, C138.2, C139.2, C140.2, C141.2, C142.2, C143.2, C144.2, C145.2, C146.2, C147.2, C148.2, C150.2, C151.2, C152.2, C157.2, C158.2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
NET_U1_A2: R19.1, U1.A2
NET_U1_A5: R22.1, U1.A5
NET_U1_AE17: R24.1, U1.AE17
NET_U1_B5: R23.1, U1.B5
NET_U1_C11: R8.1, U1.C11, U36.4
NET_U1_C14: R20.1, U1.C14
NET_U1_D4: R16.1, U1.D4
NET_U1_D19: U31.3, U31.4
NET_U1_E8: C29.1, C30.1, U1.E8
NET_U1_E11: R26.1, U1.E11
NET_U1_E12: R27.1, U1.E12
NET_U1_F9: C53.1, C54.1, U1.F9
NET_U1_G4: R17.1, U1.G4
NET_U1_G7: C47.1, C48.1, R34.1, U1.G7
NET_U1_G8: C45.1, C46.1, R33.1, U1.G8
NET_U1_G9: C19.1, C20.1, U1.G9
NET_U1_G12: C51.1, C52.1, R36.1, U1.G12
NET_U1_G13: C49.1, C50.1, R35.1, U1.G13
NET_U1_H6: R25.1, U1.H6
NET_U1_H7: C43.1, C44.1, R32.1, U1.H7
NET_U1_H10: C15.1, C16.1, C17.1, C18.1, R28.2, R29.2, R31.2, R34.2, R36.2, U1.H10, U1.J10
NET_U1_H11: C65.1, C66.1, C67.1, C68.1, C69.1, C70.1, C71.1, C72.1, C73.1, C74.1, C75.1, C76.1, C77.1, C78.1, C79.1, C80.1, C81.1, C82.1, C83.1, C84.1, C85.1, C86.1, C87.1, U1.H11, U1.H13, U1.J11, U1.J13, U1.K11, U1.L11, U1.M11, U1.N11, U1.P11, U1.R11
NET_U1_H13: U1.J13, U1.K13, U1.L13, U1.M13, U1.N13, U1.P13, U1.R13
NET_U1_H17: C93.1, C94.1, C95.1, C96.1, C97.1, C98.1, C99.1, C100.1, U1.H17, U1.J17, U1.K17, U1.L17, U1.M17, U1.N17, U1.P17
NET_U1_J1: R18.1, U1.J1
NET_U1_K1: C55.1, R1.1, U1.K1
NET_U1_K2: R21.1, U1.K2
NET_U1_K7: C23.1, R28.1, U1.K7
NET_U1_K9: U1.L9, U1.M9, U1.N9, U1.P9, U1.R9, U1.T9, U1.U9
NET_U1_L7: C39.1, C40.1, R30.1, U1.L7
NET_U1_M7: C41.1, C42.1, R31.1, U1.M7
NET_U1_R10: C8.1, C9.1, C10.1, C11.1, C12.1, C13.1, C14.1, U1.N12, U1.R10, U1.T10, U1.T13, U1.T14, U1.U10, U1.U13, U1.U14
NET_U1_U14: R30.2, R32.2, R33.2, R35.2, U1.U14
NET_U1_V7: C37.1, C38.1, R29.1, U1.V7
NET_U2_1: R10.1, U2.1, U38.4
NET_U2_2: R14.1, U2.2
NET_U2_4: U1.C12, U2.4
NET_U3_1: R11.1, U3.1, U39.4
NET_U3_2: R15.1, U3.2
NET_U3_4: U1.F12, U3.4
NET_U4_19: R9.1, U4.19, U37.4
NET_U5_18: U5.18, U5.19
NET_U6_15: R5.1, U6.15, U33.4
NET_U6_38: R50.1, U6.38
NET_U6_39: R51.1, U6.39
NET_U6_40: R49.1, U6.40
NET_U7_4: R6.1, U7.4, U34.4
NET_U7_20: R52.1, U7.20
NET_U8_B4: R56.1, U8.B4
NET_U8_B5: R7.1, U8.B5, U35.4
NET_U9_20: C125.1, C130.1, U9.20
NET_U10_2: C118.1, R59.1, U10.2
NET_U10_5: C117.1, R58.1, U10.5
NET_U11_5: C119.1, C120.1, R60.1, R61.1, U11.5
NET_U18_4: R62.2, R63.1, U18.4
NET_U19_1: C140.1, U19.1
NET_U19_6: R65.2, R66.1, U19.6
NET_U19_8: R64.1, U19.8
NET_U20_1: C143.1, U20.1
NET_U20_6: R68.2, R69.1, U20.6
NET_U20_8: R67.1, U20.8
NET_U21_1: I1.1, U21.1
NET_U21_5: R70.1, U21.5
NET_U21_6: R71.1, U21.6
NET_U21_8: C148.1, U21.8
NET_U22_1: C153.1, R73.1, R74.1, R75.1, R76.1, U22.1, U22.8
NET_U22_2: C152.1, U22.2
NET_U22_3: C153.2, C154.1, C154.2, U22.3
NET_U22_5: R77.1, U22.5
NET_U22_10: C150.1, U22.10
NET_U22_12: C149.1, I2.1, U22.12
NET_U22_14: C149.2, U22.14
NET_U22_15: R78.1, R79.1, U22.15
NET_U22_ATNET_3: I2.2, R73.2
NET_U22_ATNET_4: C154.2, R75.2
NET_U23_4: R80.2, R81.1, U23.4
NET_U24_1: C161.1, U24.1
NET_U24_6: R83.2, R84.1, U24.6
NET_U24_8: R82.1, U24.8
NET_U25_3: C166.2, I3.1, U25.3, U25.4
NET_U25_6: C166.1, U25.6
NET_U25_7: C165.1, U25.7, U25.12
NET_U25_10: R87.1, U25.10
NET_U25_11: R85.1, R86.1, U25.11
NET_U25_ATNET_3: I3.2, R86.2
NET_U26_3: R97.1, U26.3
NET_U26_6: R92.1, U26.6
NET_U26_7: R93.1, U26.7
NET_U26_8: R94.1, U26.8
NET_U26_9: R95.1, U26.9
NET_U26_16: R96.1, R101.1, U26.16
NET_U26_18: R91.1, U26.18
NET_U26_19: R90.1, U26.19, U26.20
NET_U26_21: R88.1, R89.1, U26.21, U33.2, U34.2, U35.2, U36.2, U37.2, U38.2, U39.2
NET_U26_26: C171.1, U26.26
NET_U26_27: C170.1, U26.27
NET_U26_28: C172.1, U26.28
NET_U26_30: R100.1, U26.30
NET_U26_32: R99.1, U26.32
NET_U26_38: R98.1, U26.38
NET_U27_3: U26.2, U27.3
NET_U28_3: U26.37, U28.3
NET_U29_3: U26.31, U29.3
NET_U30_3: U26.29, U30.3
NET_U31_1: R3.1, U31.1, U31.2
PROC_AUD4_RXD: U1.W24, U9.10
PROC_AUD4_TXC: U1.U22, U9.7
PROC_AUD4_TXD: U1.T20, U9.8
PROC_AUD4_TXFS: U1.V24, U9.9, U9.11
PROC_CSI0_DAT4: U1.N1, U4.18
PROC_CSI0_DAT5: U1.P2, U4.17
PROC_CSI0_DAT6: U1.N4, U4.16
PROC_CSI0_DAT7: U1.N3, U4.15
PROC_CSI0_DAT8: U1.N6, U4.14
PROC_CSI0_DAT9: U1.N5, U4.13
PROC_CSI0_DAT10: U1.M1, U4.12
PROC_CSI0_DAT11: U1.M3, U4.11
PROC_CSI0_DAT12: U1.M2, U4.10
PROC_CSI0_DAT13: U1.L1, U4.9
PROC_CSI0_HSYNC: U1.P4, U4.6
PROC_CSI0_PIXCLK: U1.P1, U4.7
PROC_CSI0_VSYNC: U1.N2, U4.5
PROC_DSI_CLK0M: U1.H3, U7.13
PROC_DSI_CLK0P: U1.H4, U7.14
PROC_DSI_D0M: U1.G2, U7.7
PROC_DSI_D0P: U1.G1, U7.8
PROC_DSI_D1M: U1.H2, U7.10
PROC_DSI_D1P: U1.H1, U7.11
PROC_EIM_A16: U1.H25, U8.E7
PROC_EIM_A17: U1.G24, U8.B3
PROC_EIM_A18: U1.J22, U8.C4
PROC_EIM_A19: U1.G25, U8.D5
PROC_EIM_A20: U1.H22, U8.D4
PROC_EIM_A21: U1.H23, U8.C5
PROC_EIM_A22: U1.F24, U8.B8
PROC_EIM_A23: U1.J21, U8.C8
PROC_EIM_A24: U1.F25, U8.F8
PROC_EIM_CS0: R53.1, U1.H24, U8.F2
PROC_EIM_D16: U1.C25, U8.E3
PROC_EIM_D17: U1.F21, U8.H3
PROC_EIM_D18: U1.D24, U8.E4
PROC_EIM_D19: U1.G21, U8.H4
PROC_EIM_D20: U1.G20, U8.H5
PROC_EIM_D21: U1.H20, U8.E5
PROC_EIM_D22: U1.E23, U8.H6
PROC_EIM_D23: U1.D25, U8.E6
PROC_EIM_D24: U1.F22, U8.F3
PROC_EIM_D25: U1.G22, U8.G3
PROC_EIM_D26: U1.E24, U8.F4
PROC_EIM_D27: U1.E25, U8.G4
PROC_EIM_D28: U1.G23, U8.F5
PROC_EIM_D29: U1.J19, U8.G6
PROC_EIM_D30: U1.J20, U8.F6
PROC_EIM_D31: U1.H21, U8.G7
PROC_EIM_DA0: U1.L20, U8.E2
PROC_EIM_DA1: U1.J25, U8.D2
PROC_EIM_DA2: U1.L21, U8.C2
PROC_EIM_DA3: U1.K24, U8.A2
PROC_EIM_DA4: U1.L22, U8.B2
PROC_EIM_DA5: U1.L23, U8.D3
PROC_EIM_DA6: U1.K25, U8.C3
PROC_EIM_DA7: U1.L25, U8.A3
PROC_EIM_DA8: U1.L24, U8.B6
PROC_EIM_DA9: U1.M21, U8.A6
PROC_EIM_DA10: U1.M22, U8.C6
PROC_EIM_DA11: U1.M20, U8.D6
PROC_EIM_DA12: U1.M24, U8.B7
PROC_EIM_DA13: U1.M23, U8.A7
PROC_EIM_DA14: U1.N23, U8.C7
PROC_EIM_DA15: U1.N24, U8.D7
PROC_EIM_EB0: R57.1, U1.K21, U8.F7
PROC_EIM_OE: R54.1, U1.J24, U8.G2
PROC_EIM_RW: R55.1, U1.K20, U8.A5
PROC_EIM_WAIT: U1.M25, U8.A4
PROC_LCD_CS: R48.1, U1.N20, U6.9
PROC_LCD_DATA00: U1.P24, U6.17
PROC_LCD_DATA01: U1.P22, U6.18
PROC_LCD_DATA02: U1.P23, U6.19
PROC_LCD_DATA03: U1.P21, U6.20
PROC_LCD_DATA04: U1.P20, U6.21
PROC_LCD_DATA05: U1.R25, U6.22
PROC_LCD_DATA06: U1.R23, U6.23
PROC_LCD_DATA07: U1.R24, U6.24
PROC_LCD_DATA08: U1.R22, U6.25
PROC_LCD_DATA09: U1.T25, U6.26
PROC_LCD_DATA10: U1.R21, U6.27
PROC_LCD_DATA11: U1.T23, U6.28
PROC_LCD_DATA12: U1.T24, U6.29
PROC_LCD_DATA13: U1.R20, U6.30
PROC_LCD_DATA14: U1.U25, U6.31
PROC_LCD_DATA15: U1.T22, U6.32
PROC_LCD_RD_E: U1.N21, U6.11
PROC_LCD_RS: U1.N25, U6.10
PROC_LCD_WR_RWN: U1.N19, U6.12
PROC_SD1_CD_B: R38.1, U5.2
PROC_SD1_CLK: R37.1, U5.8
PROC_SD1_DATA0: R40.1, U5.4
PROC_SD1_DATA1: R41.1, U5.3
PROC_SD1_DATA2: R42.1, U5.15
PROC_SD1_DATA3: R43.1, U5.14
PROC_SD1_DATA4: R44.1, U5.13
PROC_SD1_DATA5: R45.1, U5.11
PROC_SD1_DATA6: R46.1, U5.7
PROC_SD1_DATA7: R47.1, U5.5
PROC_SD1_WP: R39.1, U5.1
VCC_5V6: C168.1, C169.1, C173.1, C174.1, J1.1, R88.2, R90.2, R91.2, R101.2, U26.11, U26.22, U27.1, U27.2, U27.6, U27.7, U28.1, U28.2, U28.6, U28.7, U29.1, U29.2, U29.6, U29.7, U30.1, U30.2, U30.6, U30.7
VCC_S1_5V6: C136.1, C137.1, C141.1, C144.1, C146.1, I1.2, R64.2, R67.2, R70.2, U18.5, U18.8, U19.4, U20.4, U21.3, U21.4, U27.4, U27.5
VCC_S2_5V6: C151.1, R78.2, U22.9, U28.4, U28.5
VCC_S3_5V6: C157.1, C158.1, U23.5, U23.8, U29.4, U29.5
VCC_S4_5V6: C162.1, C164.1, R82.2, U24.4, U25.15, U25.16, U30.4, U30.5
VCC_TIER1_1V5: C138.1, C139.1, R62.1, U7.29, U18.1
VCC_TIER1_2V8: C112.1, C113.1, C114.1, C142.1, R65.1, U7.16, U7.21, U7.22, U7.23, U19.5
VCC_TIER1_3V3: C7.1, C105.1, C106.1, C110.1, C115.1, C116.1, C133.1, C134.1, C135.1, C145.1, C175.1, C176.1, C177.1, C178.1, C179.1, C180.1, C181.1, R6.2, R7.2, R8.2, R10.2, R11.2, R13.2, R26.2, R37.2, R38.2, R39.2, R40.2, R41.2, R42.2, R43.2, R44.2, R45.2, R46.2, R47.2, R53.2, R54.2, R55.2, R56.2, R57.2, R68.1, U1.G11, U2.5, U3.5, U5.9, U7.2, U8.D8, U8.F1, U8.G5, U15.4, U16.4, U17.6, U20.5, U33.5, U34.5, U35.5, U36.5, U37.5, U38.5, U39.5
VCC_TIER1_12V0: C111.1, C147.1, R71.2, U7.30, U21.7
VCC_TIER2_1V275: C88.1, C89.1, C90.1, C91.1, C92.1, C101.1, C102.1, C103.1, I2.2, R73.2, U1.H14, U1.H16, U1.J14, U1.J16, U1.K9, U1.K14, U1.K16, U1.L9, U1.L14, U1.L16, U1.M14, U1.M16, U1.N14, U1.N16, U1.P14, U1.P16, U1.R14, U1.R16, U1.T16, U1.U16
VCC_TIER3_2V8: C5.1, C6.1, C159.1, C160.1, R80.1, U1.H9, U1.J9, U23.1
VCC_TIER4_1V5: C31.1, C56.1, C57.1, C58.1, C59.1, C60.1, C61.1, C62.1, C63.1, C64.1, C163.1, R83.1, U1.G18, U1.R18, U1.T18, U1.U18, U1.V9, U1.V10, U1.V11, U1.V12, U1.V13, U1.V14, U1.V15, U1.V16, U1.V17, U1.V18, U24.5
VCC_TIER4_3V3: C21.1, C22.1, C24.1, C25.1, C26.1, C27.1, C28.1, C32.1, C33.1, C34.1, C35.1, C36.1, C104.1, C107.1, C108.1, C109.1, C121.1, C122.1, C123.1, C124.1, C126.1, C127.1, C128.1, C129.1, C167.2, I3.2, R1.2, R5.2, R9.2, R12.2, R48.2, R49.2, R50.2, R86.2, U1.G14, U1.G15, U1.G16, U1.G17, U1.J7, U1.K19, U1.L19, U1.M19, U1.N7, U1.P7, U1.P19, U1.R19, U4.1, U6.6, U6.7, U6.35, U9.3, U9.5, U9.12, U9.18, U25.8

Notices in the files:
parts and their libraries:
circuit_tree: (C) 2014 Tomasz Boleslaw CEDRO, cederom@tlen.pl, http://www.tomek.cedro.info.
